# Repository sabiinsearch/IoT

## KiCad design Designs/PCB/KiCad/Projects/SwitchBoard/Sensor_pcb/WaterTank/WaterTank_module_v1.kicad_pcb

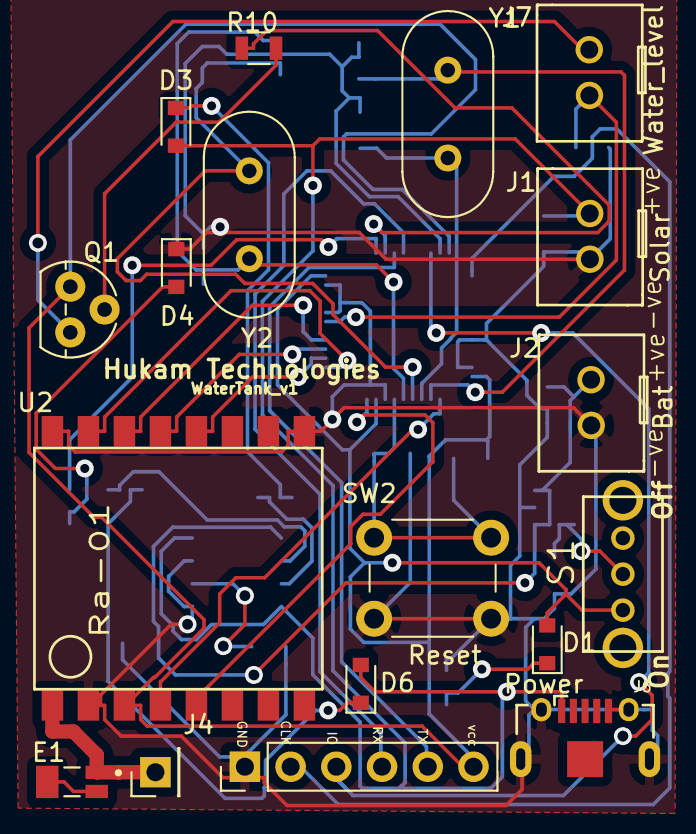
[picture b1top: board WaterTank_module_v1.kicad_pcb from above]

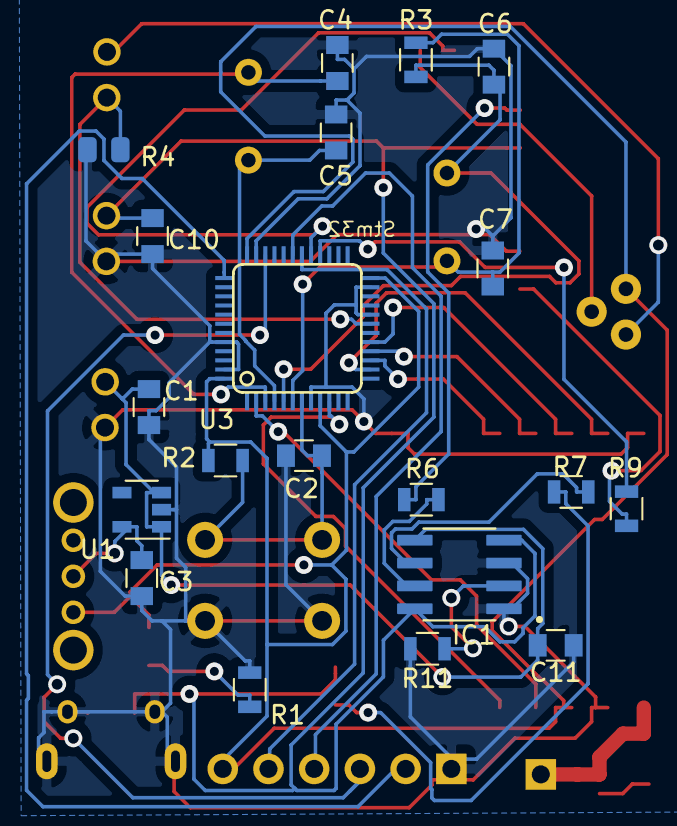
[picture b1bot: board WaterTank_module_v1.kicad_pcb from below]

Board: 2 copper layers, 38 parts (20 on the bottom side), 34 nets.

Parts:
AE1: Antenna; Pin_Header_Straight_1x01_Pitch2.54mm
C1, C3: 100 nf; C_0805
C2: 1.0uf; C_0805
C4, C5, C6, C7: 20pf; C_0805
C10, C11: 10uf; C_0805
D1, D3, D6: Pwr_L.E.D; D_0805
D4: Bat_Low; D_0805
E1: YC0009AA; XCVR_YC0009AA
IC1: TP4056
J1: Solar_input; Battery_holder
J2: Battery_input; Battery_holder
J4: Conn_01x06_Female; Pin_Header_Straight_1x06_Pitch2.54mm
J6: USB3130-XX-X_REVD; Conn_USBmicro-B_ebay-side_TH
J7: Water_level; Battery_holder
Q1: BC547
R1, R9: 510 R; R_0805
R2: 10K; R_0805
R3: 1M; R_0805
R4: 1k; R_0805_2012Metric
R6, R7, R10: 1K; R_0805
R11: 510R; R_0805
S1: OS102011MA1QN1; slide_switch_SPDT
SW2: SW_Push; SW_PUSH_6mm_h5mm
U1: APK2112.K-3.3; SOT-23-5
U2: Ra-01; LoRa
U3: STM32; STM32(LQFP48)
Y1: 32.768K; Crystal_HC49-4H_Vertical
Y2: 8Mhz; Crystal_HC49-4H_Vertical

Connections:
/Activate: R10.1, U3.29
/BAT_IN: C1.2, C11.2, IC1.5, J2.2, U1.1, U1.3
/DIO0: U2.5, U3.10
/GND: C1.1, C2.1, C3.1, C4.2, C5.2, C6.2, C7.2, C10.2, C11.1, D4.1, IC1.1, IC1.3, J1.1, J2.1, J4.1, J6.5, J6.6, R1.2, R4.2, R11.2, SW2.1, U1.2, U2.2, U2.9, U2.16, U3.8, U3.20, U3.23, U3.35, U3.44, U3.47
/MISO: U2.13, U3.16
/MOSI: U2.14, U3.17
/NSS: U2.15, U3.14
/OSCIN: C6.1, R3.1, U3.5, Y2.1
/OSCOUT: C7.1, R3.2, U3.6, Y2.2
/PC14: C4.1, U3.3, Y1.1
/PC15: C5.1, U3.4, Y1.2
/RESET: C2.2, R2.2, SW2.2, U3.7
/RX: J4.4, U3.31
/Reset_LoRa: U2.4, U3.2
/SCK: U2.12, U3.15
/SWCLK: J4.2, U3.37
/SWIO: J4.3, U3.34
/Solar_+ve: C10.1, D3.2, D6.2, IC1.4, IC1.8, J1.2, J6.1
/Supply_Reg: C3.2, S1.2, U1.5
/TX: J4.5, U3.30
/VCC3V3: D1.2, J4.6, Q1.2, R2.1, S1.1, U2.3, U3.9, U3.24, U3.36, U3.48
/VCC3V3_Sensor: J7.2, Q1.3
/frmSensor: J7.1, R4.1, U3.19
unnamed: AE1.1, E1.1, U2.1
unnamed: D1.1, R1.1
unnamed: D3.1, R6.2
unnamed: D4.2, R9.1
unnamed: D6.1, R7.2
unnamed: E1.2, E1.3
unnamed: IC1.2, R11.1
unnamed: IC1.6, R7.1
unnamed: IC1.7, R6.1
unnamed: Q1.1, R10.2
unnamed: R9.2, U3.28

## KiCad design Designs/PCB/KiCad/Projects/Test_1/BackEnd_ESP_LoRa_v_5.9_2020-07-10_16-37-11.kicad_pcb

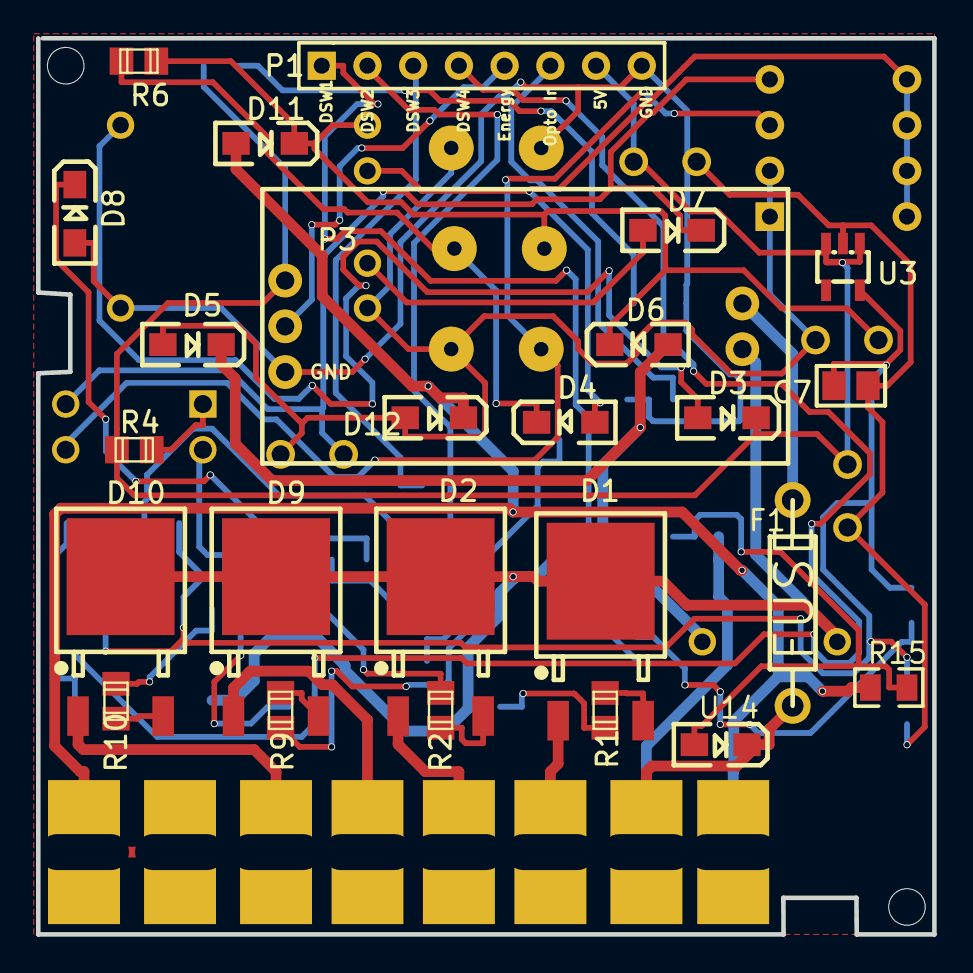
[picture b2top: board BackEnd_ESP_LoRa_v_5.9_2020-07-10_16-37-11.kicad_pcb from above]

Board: 2 copper layers, 49.8 x 49.8 mm, 57 parts (0 on the bottom side), 43 nets.

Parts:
C1, C6: 470uF/10V; CAP-D8.0XF3.5
C2: 1uF/63V; CAP-D8.0XF3.5
C3: 47nf; CAP_10NF_2A103J
C4: 4.7uF/400V; CAP-D8.0XF3.5
C5, C8: 2A222J / 2.2nF; CAP_10NF_2A103J
C7: 2.2uF; C0805
D1, D2, D9, D10: BT1; BT136S
D3: SR360; DIODES_PICK_HUKAM
D4: FR107; DIODES_PICK_HUKAM
D5, D6, D11, D12: IN4007; DIODES_PICK_HUKAM
D7: IN4148; DIODES_PICK_HUKAM
D8: PH C4V3; DIODES_PICK_HUKAM
F1: FUSE thermal; FUSE THERMAL
J1, J2, J3, J4, J5, J6, J7, J8: Terminal; SCREW_TERMINAL-5MM
LED1: LED; DIODES_PICK
NTC: 10D-9; DIP-10.5*5.5MM
P1: Header-Female-2.54_1x8; HDR-8X1/2.54
P3: CurrentSensor; LOW CURRENT SENSOR - ACS712
R1, R2, R9, R10: 470 E; R_0805
R3: 2.2K; R_0805
R4, R5: 330 Ohm; R_0805
R6: 100K; R_0805
R7: 0E; R0805
R11, R12, R13, R14: 100 E; R_0805
R15: 220k; 0805
T1: Transformer - EE16-1; TRANSFORMER_SMPS_HUKKAM
U1, U2, U9, U10: MOC_sw1; DIL06-SMD
U3: AP2112K-3.3TRG; SOT23-5
U4: AP8022; DIP-8
U5: EL817; DIP-4
U13: 4N35; DIL06-SMD
U14: Zener - 4148; DIODES_PICK

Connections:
3.3V: C7.1, R7.2, R11.2, R12.2, R13.2, R14.2, U3.5
5V: C1.1, C6.1, D3.2, P1.7, P3.3, R3.2, R4.1, U3.1, U3.3
C5_1: C5.1, D4.2, R6.2
D1_3: D1.3, R1.1
D2_3: D2.3, R2.2
D9_3: D9.3, R9.2
D10_3: D10.3, R10.2
DSW1: P1.1, U1.2
DSW2: P1.2, U2.2
DSW3: P1.3, U9.2
DSW4: P1.4, U10.2
ENERGY_SENSOR: P1.5, P3.4
GND: C1.2, C6.2, C7.2, C8.1, D8.1, LED1.2, P1.8, P3.5, R7.1, T1.5, U3.2, U13.4
LED1_1: LED1.1, R3.1
MAINS_LIVE_IN: F1.1, J2.1, U13.1, U14.2
MAINS_LIVE_OUT: D1.4, D2.4, D9.4, D10.4, NTC.1, P3.1, U1.6, U2.6, U9.6, U10.6
MAINS_NEUTRAL: D11.1, D12.2, J1.1, J3.1, J4.1, R15.2
NTC_2: D5.2, D6.1, NTC.2
OPTO_IN: P1.6, U13.5
OUT1: D1.1, J5.1
OUT2: D2.1, J6.1
OUT3: D9.1, J7.1
OUT4: D10.1, J8.1
P3_2: F1.2, P3.2
R5_1: D8.2, R5.1
T1_1: C4.1, C5.2, D6.2, D11.2, R6.1, T1.1
T1_2: D4.1, T1.2, U4.5, U4.6, U4.7, U4.8
T1_3: D7.1, T1.3
T1_4: C2.2, C3.2, C4.2, C8.2, D5.1, D12.1, T1.4, U4.1, U4.2
T1_6: D3.1, T1.6
U1_1: R11.1, U1.1
U1_4: R1.2, U1.4
U2_1: R12.1, U2.1
U2_4: R2.1, U2.4
U4_3: C3.1, U4.3, U5.3
U4_4: C2.1, D7.2, U4.4, U5.4
U5_1: R4.2, U5.1
U5_2: R5.2, U5.2
U9_1: R13.1, U9.1
U9_4: R9.1, U9.4
U10_1: R14.1, U10.1
U10_4: R10.1, U10.4
U13_2: R15.1, U13.2, U14.1

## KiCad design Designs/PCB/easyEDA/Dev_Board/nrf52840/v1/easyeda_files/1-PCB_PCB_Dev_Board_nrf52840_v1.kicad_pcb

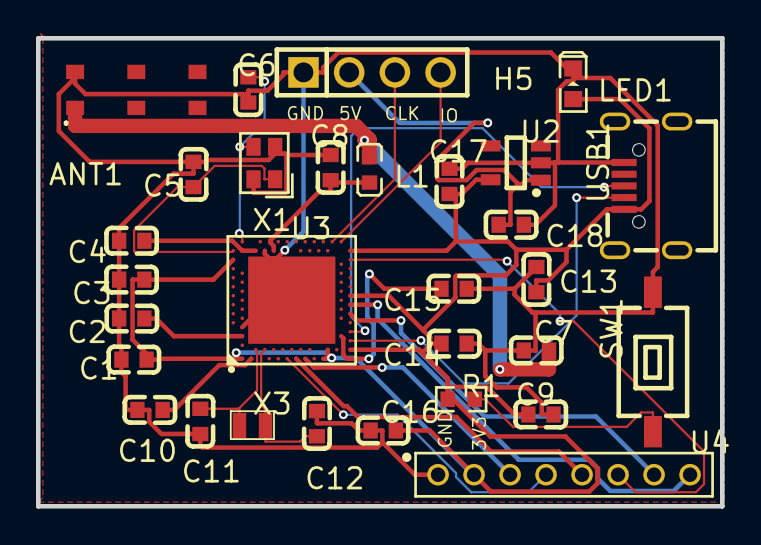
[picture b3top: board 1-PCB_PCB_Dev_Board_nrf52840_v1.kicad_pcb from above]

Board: 2 copper layers, 38.0 x 26.0 mm, 30 parts (0 on the bottom side), 24 nets.

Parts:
ANT1: M830520
C1, C2: 1uf; C0603
C3, C9, C10, C16: 100nf; C0603
C4: 100pf; C0603
C5, C6, C11, C12: 12pf; C0603
C7: 0.5pf; C0603
C8: 0.8pf; C0603
C13, C14, C15: 4.7uf; C0603
C17, C18: 10uf; C0603
H5: Programming Headers; HDR-TH_4P-P2.54-V-M
L1: 3.3nH; L0603
LED1: LED_Pwr; LED0603_RED
R1: 10k; R0603
SW1: Reset_Button; SW-SMD_L6.0-W3.7-LS8.0
U2: AP2112K-3.3TRG1; SOT-25-5_L3.0-W1.8-P0.95-LS3.0-BR
U3: NRF52840-QIAA-R7; AQFN-73_L7.0-W7.0-P0.50-BL-EP4.8
U4: Header_8x1; CONN-TH_8P-P2.00_KINGHELM_KH-2FH-1X8P-H4.3
USB1: MICRO 4P DIP; MINI-USB-SMD_MICRO-4P-DIP
X1: 32MHz; OSC-SMD_4P-L2.0-W1.6-BL
X3: 32MHz; ABS06-107-32.768KHZ-T

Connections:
5V: C18.1, H5.2, U2.1
ANT1_1: ANT1.1, C7.2, L1.1
CRYSTAL_1: C11.1, U3.D2, X3.1
CRYSTAL_2: C12.2, U3.F2, X3.2
D+: U3.AD6, USB1.3
D-: U3.AD4, USB1.2
GND: ANT1.2, C1.1, C2.2, C3.1, C4.1, C5.1, C6.2, C7.1, C8.1, C9.2, C10.1, C11.2, C12.1, C13.1, C14.1, C15.2, C16.1, C17.2, C18.2, H5.1, LED1.2, SW1.2, U2.2, U3.0, U3.B7, U3.F23, U4.1, USB1.5, X1.2, X1.4
HDR__1: U3.R1, U4.3
HDR__2: U3.L1, U4.4
HDR__3: U3.N1, U4.5
HDR__4: U3.AD22, U4.6
HDR__5: U3.AD10, U4.7
HDR__6: U3.AD12, U4.8
RESET: R1.1, SW1.1
SWDCLK: H5.3, U3.AA24
SWDIO: H5.4, U3.AC24
U3_AC5: C15.1, U3.AC5
U3_B5: C2.1, U3.B5
U3_C1: C10.2, U3.C1
U3_D23: C4.2, U3.D23
U3_H23: C8.2, L1.2, U3.H23
VDD_P3V3: C1.2, C3.2, C9.1, C13.2, C14.2, C16.2, C17.1, LED1.1, R1.2, U2.5, U3.A22, U3.AD2, U3.AD14, U3.AD23, U3.B1, U3.W1, U3.Y2, U4.2, USB1.1
XTAL_1: C6.1, U3.B24, X1.3
XTAL_2: C5.2, U3.A23, X1.1

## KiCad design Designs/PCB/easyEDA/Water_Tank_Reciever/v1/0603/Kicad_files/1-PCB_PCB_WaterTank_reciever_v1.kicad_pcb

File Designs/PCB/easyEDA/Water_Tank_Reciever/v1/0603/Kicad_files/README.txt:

receives the data from Water Tank and Switch on Water pump to motor            
How to use：

At editor, Click the document icon on the topbar, via "Document" > "Open" > "EasyEDA Source", and select json file, then open it at the editor.

如何使用：

在编辑器顶部工具栏，点击“文档”图标，选择 “文档” > “打开” > “EasyEDA源码”，选择json文件打开即可。

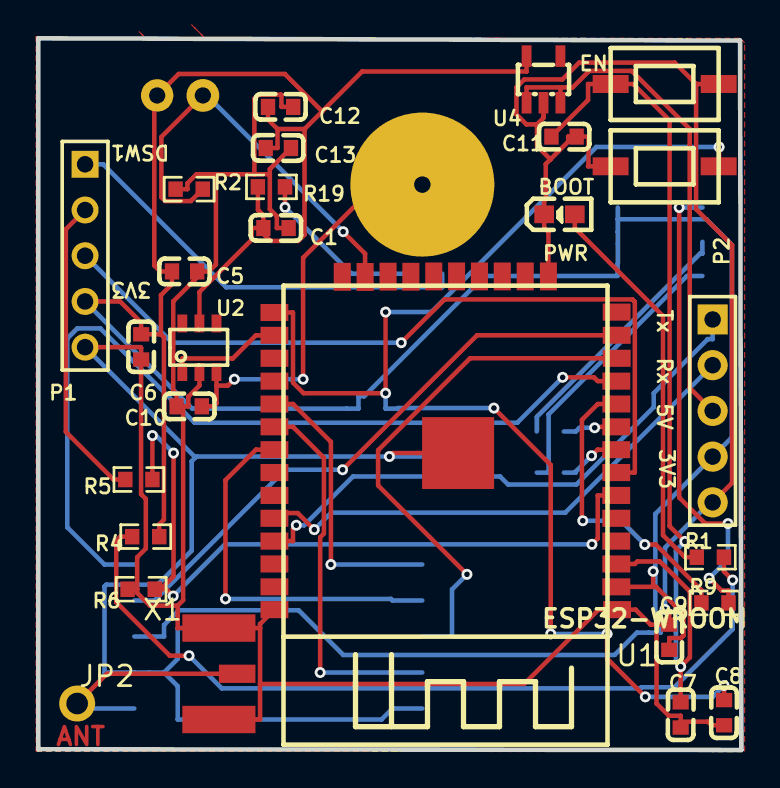
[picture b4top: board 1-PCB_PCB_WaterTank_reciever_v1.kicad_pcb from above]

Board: 2 copper layers, 39.1 x 39.5 mm, 36 parts (0 on the bottom side), 30 nets.

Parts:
.: JST_Conn_Water_Level; JST XH2.5MM PCB CONNECTOR
BOOT: SW1; KEY-3.7*6.1
C1: 2.2uF; C0603
C5: 100uF; C0603
C6, C7, C8, C11, C12: 0.1uF; C0603
C9, C13: 10uF; C0603
C10: 22pF; C0603
EN: SW2; KEY-3.7*6.1
JP2: ANT; ANTENA
LED_SW: LED_Indicator; LED-0603
P1: Ext_HDR; HDR1X5
P2: HDR1X5; HDR1X5 FIX
PWR: LED-Blue(0603); LED-0603
R1, R5, R6, R9, R10, R14, R19: 1K; R0603
R2: 1k; R0603
R4: 0E; R0603
R7: 10k; R0603
R8: 5K; R0603
STATUS: 5050QRC; RGB-5050
T1: CapTouch Pad; TOUCHPADROUND_V1
U1: ESP32-WROOM; ESP32-WROOM FOOTPRINT
U2: TTP223E-BA6; SOT-23-6
U4: AP2112K-3.3TRG; SOT23-5
U5: .; RA-02
X1: .; SMA_EDGELAUNCH_UFL

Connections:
3.3V: ..1, C1.1, C5.1, C6.1, C9.2, C12.1, C13.1, P1.4, P2.4, R4.2, R7.2, R8.1, R19.1, STATUS.1, STATUS.3, STATUS.5, U1.2, U2.5, U4.5, U5.3
BP1: U1.26, U2.1
C10_1: C10.1, T1.1, U2.3
DSW1: LED_SW.2, P1.1
EN: C7.1, C11.2, EN.2, R7.1, U1.3
ENERGY_SENSOR_3V: R5.1, R6.2, U1.6
ENERGY_SENSOR_5V: P1.2, R5.2
EXT_5V: P2.3, U4.1, U4.3
FRM_SENSOR: ..2, R2.2, U1.23
GND: BOOT.1, C1.2, C5.2, C6.2, C7.2, C8.1, C9.1, C10.2, C11.1, C12.2, C13.2, EN.1, P1.5, P2.5, PWR.2, R2.1, R6.1, U1.1, U1.15, U1.38, U1.39, U2.2, U4.2, U5.2, U5.9, U5.16, X1.GND@1, X1.GND@2, X1.GND@3, X1.GND@4
IO0: BOOT.2, C8.2, R8.2, U1.25
IO25: R9.1, U1.10
IO32: R14.1, U1.8
IO33: R10.1, U1.9
IRQ: U1.11, U5.5
JP2_1: JP2.1, U5.1, X1.P
LED_PWR_1: PWR.1, R1.2
MISO: U1.31, U5.13
MOSI: U1.12, U5.14
NSS: U1.30, U5.15
OPTO_IN: P1.3, U1.7
R1_1: R1.1, R4.1
R9_2: R9.2, STATUS.2
R10_2: R10.2, STATUS.4
R19_2: LED_SW.1, R19.2
RFM_RESET: U1.13, U5.4
RGB1_6: R14.2, STATUS.6
RXD0: P2.2, U1.34
SCK: U1.29, U5.12
TXD0: P2.1, U1.35
